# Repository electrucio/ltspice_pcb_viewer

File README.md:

# ltspice_pcb_viewer

Umbrella project for visualizing and cross-exploring electronics designs
(LTspice / KiCad schematics and PCBs). The project is composed of independent
**modules** under [`modules/`](modules/) that will be integrated into a single
application later.

## Modules

| Module | Description |
| --- | --- |
| [`kicad_schematic_viewer`](modules/kicad_schematic_viewer/) | Framework-agnostic `<kicad-schematic>` web component that parses `.kicad_sch`, computes the netlist in-browser, and renders an interactive SVG with net/component highlighting. |
| [`ltspice_schematic_viewer`](modules/ltspice_schematic_viewer/) | Framework-agnostic `<ltspice-schematic>` web component that parses `.asc` (with an embedded `.asy` symbol library), computes the netlist in-browser, and renders an interactive SVG with net/component highlighting. |
| [`ltspice_kicad_mapper`](modules/ltspice_kicad_mapper/) | `<ltspice-kicad-mapper>` web component that embeds both viewers side by side and builds a 1:1 net/component mapping between an LTspice and a KiCad schematic, with JSON import/export. The first cross-module integration. |
| [`kicad_pcb_viewer`](modules/kicad_pcb_viewer/) | `<kicad-pcb>` web component that renders a KiCad `.kicad_pcb` as a single all-layers view (layer toggles, mirror, pan/zoom) with net/component highlighting. |
| [`app`](modules/app/) | The integrated **application**: LTspice on the left, a switchable KiCad schematic/PCB on the right; map nets/components with synchronized cross-probe highlighting; **download a read-only single-file HTML** (iOS-Safari-12-compatible) of the current designs + mapping. |

_The `app` module is the first full integration; more building-block modules may still follow._

The two schematic viewers share the same interaction model and `ksv-*` theming
conventions; their net engines are cross-validated against each other on the shared
guitar-amplifier power-amp design.

## Working on a module

Each module is self-contained (its own `package.json`, build, tests, and demo):

```bash
cd modules/kicad_schematic_viewer
npm install
npm run dev     # interactive demo
npm test        # unit tests
npm run build   # library bundle in dist/
```

## Layout

```
ltspice_pcb_viewer/
  modules/
    kicad_schematic_viewer/     # KiCad schematic net/component viewer
    ltspice_schematic_viewer/   # LTspice schematic net/component viewer
    ltspice_kicad_mapper/       # side-by-side net/component mapper (embeds both viewers)
    kicad_pcb_viewer/           # KiCad .kicad_pcb viewer (all layers, toggles, highlight)
    app/                        # integrated app: map + cross-probe + read-only HTML export
  README.md
```

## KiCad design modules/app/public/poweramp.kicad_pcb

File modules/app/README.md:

# app — LTspice ↔ KiCad mapper & cross-probe

The integrated application that ties the other modules together:

- **Left:** an LTspice schematic. **Right:** a KiCad project, switchable between its
  **schematic** and its **PCB** (a `[Schematic | PCB]` toggle).
- **Map** nets and components between LTspice and KiCad, with **synchronized
  highlighting**: click a net/component in any pane and its mapped counterpart lights up
  in the others — including the PCB (KiCad schematic and PCB share refs; net names are
  reconciled, e.g. schematic `POW` ↔ PCB `/POW`).
- **Simulation summaries**: upload an LTspice transient `.raw` (+ optional `.op.raw`);
  the app summarizes each net (V min/avg/rms/max/pp, DC bias) and component (current,
  voltage drop, power; transistor Ic/Ib/Ie + β) and **discards the bulk waveform**. Hover
  any net/component (either side) to see its metrics in a tooltip; the `ƒ directives` button
  lists the SPICE directives, and the summary rides along in the exported HTML.
  Optionally **Load .log** — the `.raw` stores float32, so harmonics/THD/ripple can't be
  recomputed to LTspice's precision; instead the `.log`'s **exact** `.four` (harmonics +
  THD, signal *and* 50 Hz ripple) and `.meas` results are parsed and shown verbatim in a
  **"from LTspice .log"** section of the tooltip (`sim/logfile.ts`).
  Optionally **Load .net** (the LTspice SPICE netlist) too: unlabeled nets get
  viewer-invented names (`Net-(C14.1)`) that don't match the `.raw`'s internal node names
  (`V(n008)`), so they'd otherwise show no data; the netlist bridges them by matching each
  net to the node touching the same component set (`sim/netlist.ts`) — this also lets the
  `.log`'s node data attach to anonymous nets.
- **Upload** any `.asc`, `.kicad_sch`, and `.kicad_pcb` (toolbar Load buttons).
- **Download read-only HTML**: bakes the current designs + mapping into **one
  self-contained file** that is **read-only** (cross-probe by clicking the schematics/PCB
  or the **nets/components lists**, plus the schematic/PCB toggle and PCB **Mirror** /
  **Rotate** (90°/180°/270°) controls — no editing) and **compatible with old iOS
  Safari (12.x)**.

The app itself targets modern browsers; only the downloaded file carries the old-Safari
constraint.

## Run

```bash
npm install
npm run dev     # builds the export template, then serves the app (modern browsers)
npm run build   # dist-app/ (modern static build)
```

`npm run dev`/`build` first run `npm run build:viewer`, which compiles the read-only
viewer (`viewer/`) into a single Safari-12-targeted HTML *template*
(`src/generated/viewer.html`, git-ignored). The app imports that template with `?raw`
and, on **Download**, replaces its `__LK_DATA__` placeholder with a JSON payload of the
current designs + mapping (ibom-style data-in-a-`<script>`-block; no `fetch`).

## How the pieces fit

```
index.html + src/main.ts            app shell: toolbar (Download) + <ltspice-kicad-mapper>
  └─ <ltspice-kicad-mapper>          embeds <ltspice-schematic>, <kicad-schematic>,
                                     <kicad-pcb>; owns mapping + synchronized highlight
viewer/  (read-only export)         viewer.html + viewer.ts + cross-probe.ts
                                     + lists.ts (read-only sidebars) + compat.ts
  └─ compiled by vite.viewer.config.ts (target: safari12) → src/generated/viewer.html
```

### Old-Safari compatibility (export only)

- `vite.viewer.config.ts` sets esbuild `build.target: "safari12"` → modern **syntax**
  (`?.`, `??`, …) is downleveled automatically.
- `viewer/compat.ts` shims the two **method**-level gaps the viewer components use that
  esbuild does not polyfill: `Element.prototype.replaceChildren` (Safari 14+) and
  `Array.prototype.flatMap`.
- Rendering is **SVG** (no canvas `Path2D`); Web Components / Shadow DOM are native in
  iOS Safari 10.1+; no web-components polyfill is needed for the iOS 12 target.

## Deploying the app (GitHub Pages)

The app is a pure client-side SPA (no backend; static asset `fetch()` calls are
page-relative), so it can be served as-is from GitHub Pages. It's published to
`electrucio.github.io/ltspice-kicad-mapper/` by `.github/workflows/deploy-app.yml`,
which builds `modules/app` with `VITE_BASE=/ltspice-kicad-mapper/` (see `vite.config.ts`
— the built `index.html` otherwise references assets from the site **root**, which
would collide with the other content already at `electrucio.github.io`'s root) and
pushes `dist-app/` into that subfolder of the `electrucio/electrucio.github.io` repo.

One-time setup (must be done by a human on github.com — not automatable from here):

1. **Push this repo to GitHub** (it currently only exists locally): create a repo (e.g.
   under the `electrucio` account) and `git remote add origin <url> && git push -u origin main`.
2. **Create a deploy token**: a classic PAT with `repo` scope, or a fine-grained PAT
   scoped to `electrucio/electrucio.github.io` with **Contents: read and write** —
   created on the account that has push access to that repo.
3. **Add it as a secret** named `PAGES_DEPLOY_TOKEN` in this repo's
   **Settings → Secrets and variables → Actions**.
4. Push to `main` (touching `modules/app/**` or a sibling viewer module) — the workflow
   builds and deploys automatically. Use the **Run workflow** button (workflow_dispatch)
   for a manual first run.

To change the target subfolder or repo, edit `DEPLOY_SUBPATH` / the `repository:` field
in `.github/workflows/deploy-app.yml`.

## Future

The export payload reserves a `simulation` field (currently `null`) for upcoming
LTspice simulation results linked to specific nets/components.

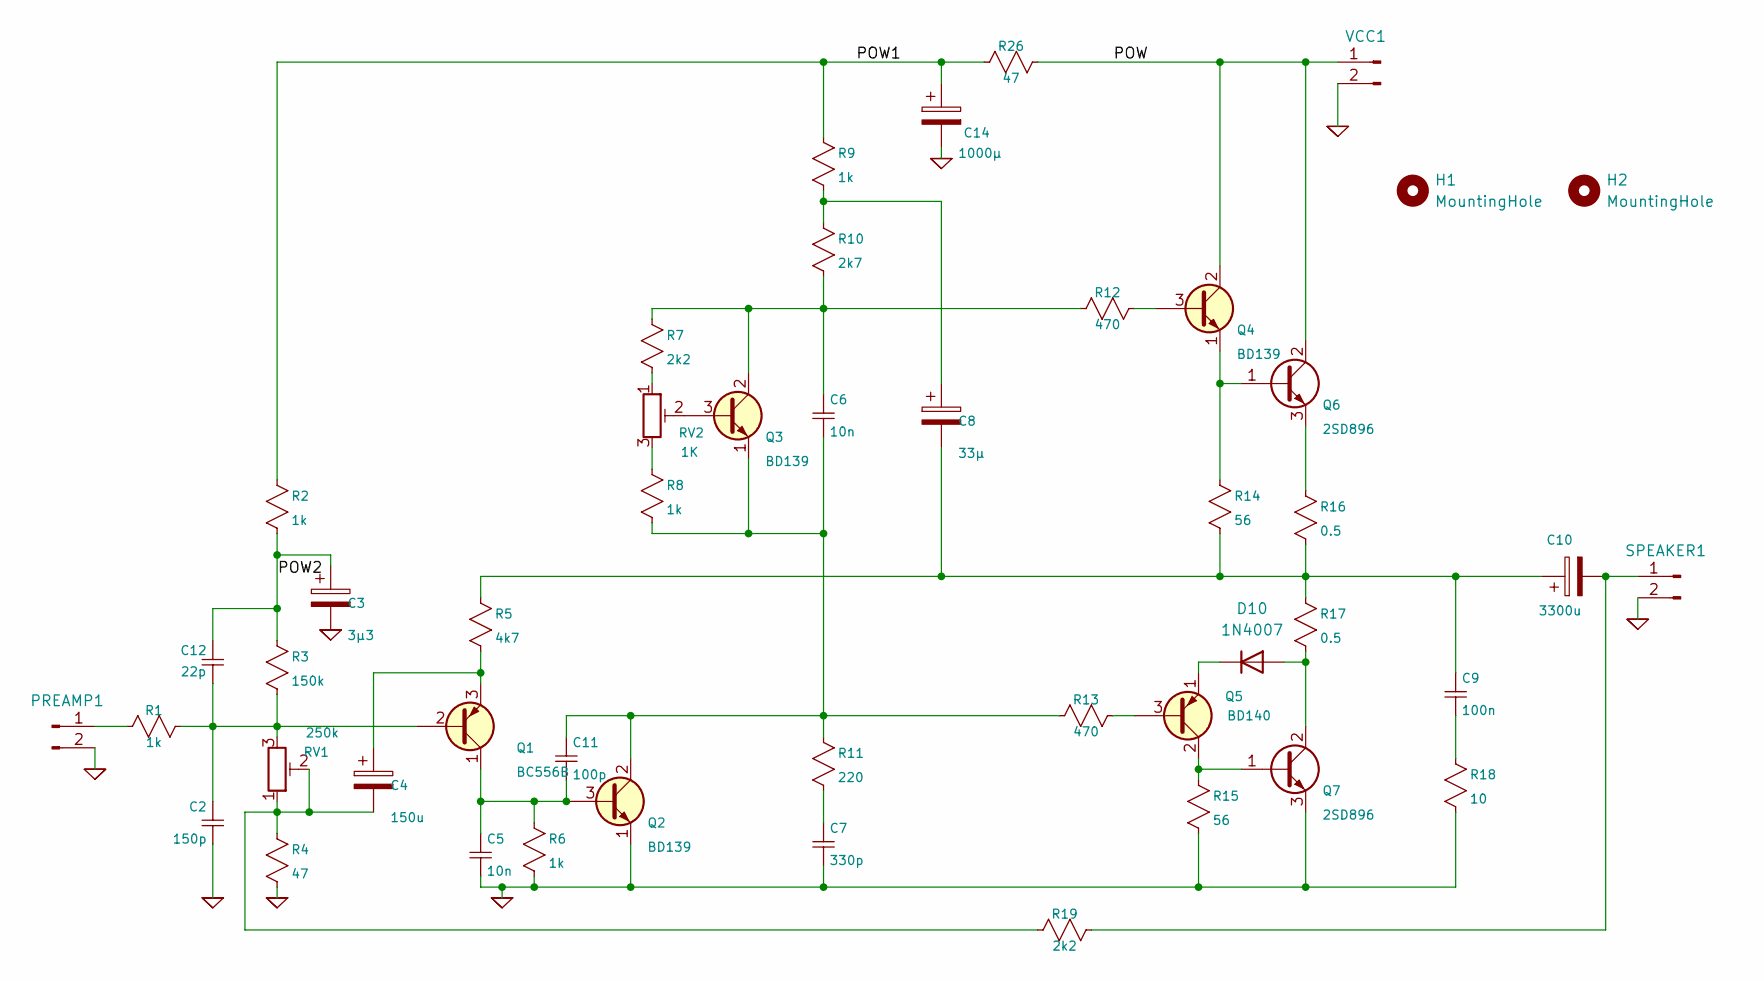
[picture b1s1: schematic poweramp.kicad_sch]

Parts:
C2: 150p; C_Rect_WIMA_1uF_CNC_LargePads
C3: 3µ3; CP_Radial_D6.3mm_P2.50mm
C4: 150u; CP_Radial_220u_8mm_3.5mm_largerpads
C5, C6: 10n; C_Rect_WIMA_1uF_CNC_LargePads
C7: 330p; C_Rect_WIMA_1uF_CNC_LargePads
C8: 33µ; CP_Radial_D8.0mm_P3.80mm
C9: 100n; C_Rect_WIMA_1uF_CNC_LargePads
C10: 3300u; CP_Radial_D22.0mm_P10.00mm_SnapIn
C11: 100p; C_Rect_WIMA_1uF_CNC_LargePads
C12: 22p; C_Disc_D4.3mm_W1.9mm_P5.00mm_largerpads
C14: 1000µ; CP_Radial_220u_12.5mm_5mm_largerpads
D10: 1N4007; D_DO-41_SOD81_P10.16mm_Horizontal
H1, H2: MountingHole; MountingHole_3.5mm
PREAMP1: JST_XH_B2B-XH-A_1x02_P2.50mm_Vertical_ovalpads
Q1: BC556B; TO-92_Inline_Wide_CBE
Q2, Q3, Q4: BD139; TO-126-3_Vertical_ECB
Q5: BD140; TO-126-3_Vertical_ECB
Q6, Q7: 2SD896; TO-3P-3_Vertical_BCE
R1, R2, R6, R8, R9: 1k; R_Axial_DIN0207_L6.3mm_D2.5mm_P10.16mm_Horizontal_LargerPads
R3: 150k; R_Axial_DIN0207_L6.3mm_D2.5mm_P10.16mm_Horizontal_LargerPads
R4: 47; R_Axial_DIN0207_L6.3mm_D2.5mm_P10.16mm_Horizontal_LargerPads
R5: 4k7; R_Axial_DIN0207_L6.3mm_D2.5mm_P10.16mm_Horizontal_LargerPads
R7, R19: 2k2; R_Axial_DIN0207_L6.3mm_D2.5mm_P10.16mm_Horizontal_LargerPads
R10: 2k7; R_Axial_DIN0207_L6.3mm_D2.5mm_P10.16mm_Horizontal_LargerPads
R11: 220; R_Axial_DIN0207_L6.3mm_D2.5mm_P10.16mm_Horizontal_LargerPads
R12, R13: 470; R_Axial_DIN0207_L6.3mm_D2.5mm_P10.16mm_Horizontal_LargerPads
R14, R15: 56; R_Axial_DIN0207_L6.3mm_D2.5mm_P10.16mm_Horizontal_LargerPads
R16, R17: 0.5; R_Axial_Power_L25.0mm_W9.0mm_P30.48mm
R18: 10; R_Axial_DIN0207_L15mm_D5mm_P22mm_Horizontal_LargerPads
R26: 47; R_Axial_DIN0207_L15mm_D5mm_P22mm_Horizontal_LargerPads
RV1: 250k; Potentiometer_Piher_PT-6-V_Vertical_largerpads
RV2: 1K; Potentiometer_Piher_PT-10-V_Vertical_largerpads
SPEAKER1: JST_XH_B2B-XH-A_1x02_P2.50mm_Vertical_ovalpads
VCC1: JST_XH_B2B-XH-A_1x02_P2.50mm_Vertical_ovalpads

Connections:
0: C2.2, C3.2, C5.2, C7.2, C14.2, PREAMP1.2, Q2.1 (E), Q7.3 (E), R4.2, R6.2, R15.2, R18.2, SPEAKER1.2, VCC1.2
/POW: Q4.2 (C), Q6.2 (C), R26.1, VCC1.1
/POW1: C14.1, R2.1, R9.1, R26.2
/POW2: C3.1, C12.1, R2.2, R3.1
unnamed: C4.2, R4.1, R19.2, RV1.1, RV1.2
unnamed: C7.1, R11.2
unnamed: C8.1, R9.2, R10.1
unnamed: C9.2, R18.1
unnamed: C8.2, C9.1, C10.1, R5.1, R14.2, R16.2, R17.1
unnamed: D10.2 (A), Q7.2 (C), R17.2
unnamed: D10.1 (K), Q5.1 (E)
unnamed: PREAMP1.1, R1.2
unnamed: C2.1, C12.2, Q1.2 (B), R1.1, R3.2, RV1.3
unnamed: C5.1, C11.2, Q1.1 (C), Q2.3 (B), R6.1
unnamed: C4.1, Q1.3 (E), R5.2
unnamed 15: C6.2, C11.1, Q2.2 (C), Q3.1 (E), R8.2, R11.1, R13.2; also elsewhere on the board
unnamed 16: Q3.3 (B), RV2.2; also elsewhere on the board
unnamed 17: C6.1, Q3.2 (C), R7.1, R10.2, R12.2; also elsewhere on the board
unnamed: Q4.3 (B), R12.1
unnamed: Q4.1 (E), Q6.1 (B), R14.1
unnamed: Q5.3 (B), R13.1
unnamed: Q5.2 (C), Q7.1 (B), R15.1
unnamed: Q6.3 (E), R16.1
unnamed: R7.2, RV2.1
unnamed: R8.1, RV2.3
unnamed: C10.2, R19.1, SPEAKER1.1

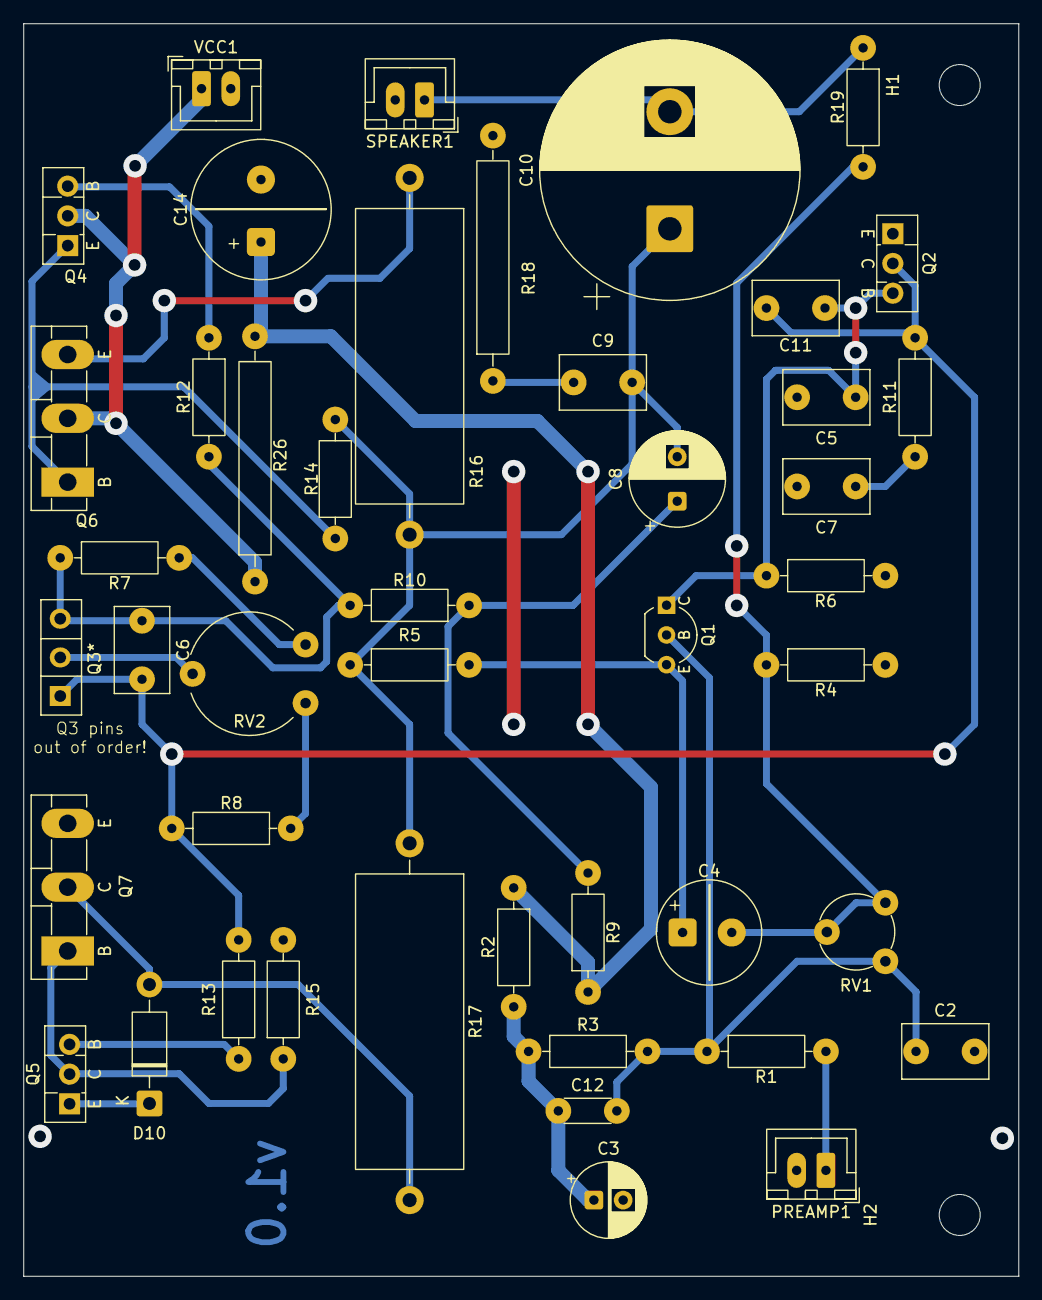
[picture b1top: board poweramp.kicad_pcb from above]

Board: 2 copper layers, 85.0 x 107.0 mm, 47 parts (0 on the bottom side), 26 nets.

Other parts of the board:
Q3*: BD139; TO-126-3_Vertical

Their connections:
unnamed 15: Q3*.1 (E); also elsewhere on the board
unnamed 16: Q3*.3 (B); also elsewhere on the board
unnamed 17: Q3*.2 (C); also elsewhere on the board

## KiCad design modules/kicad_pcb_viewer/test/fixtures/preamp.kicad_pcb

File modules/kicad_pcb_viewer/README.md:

# kicad_pcb_viewer

A framework-agnostic **web component** that renders a KiCad PCB (`.kicad_pcb`) as a
**single combined view of all layers** (not split top/bottom like InteractiveHtmlBom),
with layer toggles, net/component highlighting, mirror, and pan/zoom. Part of the
`ltspice_pcb_viewer` umbrella project; designed for later cross-probe integration.

```html
<kicad-pcb src="board.kicad_pcb"></kicad-pcb>
<script type="module">
  import "kicad_pcb_viewer"; // auto-registers <kicad-pcb>
</script>
```

## What it does

- Parses `.kicad_pcb` (S-expression, reusing the schematic viewer's `sexpr` parser) into
  a render-ready model: board edges, copper tracks, vias, zone fills, and footprints with
  pads + silkscreen + reference labels. Nets are referenced by name (KiCad 9/10).
- Renders one SVG in board mm (Y down): bottom copper, top copper, pads (with drill
  holes), vias, silkscreen, board outline, references — each in a `data-layer` group.
- Every clickable element carries `data-net` / `data-ref`; highlight reuses the
  `--ksv-highlight` variable so the umbrella app can cross-probe like the schematic viewers.

## API

- Attributes: `src`.
- Methods: `loadFromUrl`, `loadFromString`, `getLayers()`, `setLayer(layer, visible)`,
  `setMirror(on)`, `toggleMirror()`, `setRotation(deg)`, `getRotation()`, `rotate90()`,
  `fit()`, `highlightNet(name)`, `highlightComponent(ref)`, `clearHighlights()`,
  `getNets()`, `getComponents()`.
- Events: `ready`, `netselect`, `componentselect`, `nethover`.

Layer ids (toggleable): `B.Cu`, `F.Cu`, `pads`, `vias`, `B.SilkS`, `F.SilkS`,
`Edge.Cuts`, `refs`.

## Develop

```bash
npm install
npm run dev     # demo: poweramp.kicad_pcb (layer checkboxes, net/part lists, mirror)
npm test        # parser tests (counts + pad-on-track coincidence)
npm run build   # library bundle in dist/
```

## Export the demo as a static page

`npm run build:demo` bundles the demo into a **single self-contained**
`dist-demo/index.html` (JS, CSS, and the default `poweramp.kicad_pcb` all inlined —
no runtime `fetch`). It uses a relative `base`, so it works at any URL or subpath:

```bash
# bake YOUR board into the page (defaults to the bundled poweramp board):
BOARD=/path/to/your.kicad_pcb npm run build:demo

# then publish the one file anywhere static, e.g. a GitHub Pages repo:
cp dist-demo/index.html /path/to/<user>.github.io/pcb.html
# it even opens straight from file://
```

The in-page file picker still works on the static page (it reads the chosen
`.kicad_pcb` locally in the browser — nothing is uploaded), so one published
page can also view other boards on the fly.

## Notes / limitations (v1)
- The footprint/pad rotation sign (`ROT_SIGN`) is locked empirically (pads coincide with
  their nets' track endpoints). All poweramp footprints are front-side & through-hole;
  back-side footprint flipping isn't exercised yet (the parser places by orientation only).
- Pad shapes: circle / oval / roundrect / rect (trapezoid/custom fall back to rect).
- Mirror is a horizontal flip of the whole view (text included), i.e. "view from back".
- No copper-pour hatching, soldermask, or 3D; zones render as their filled polygons.

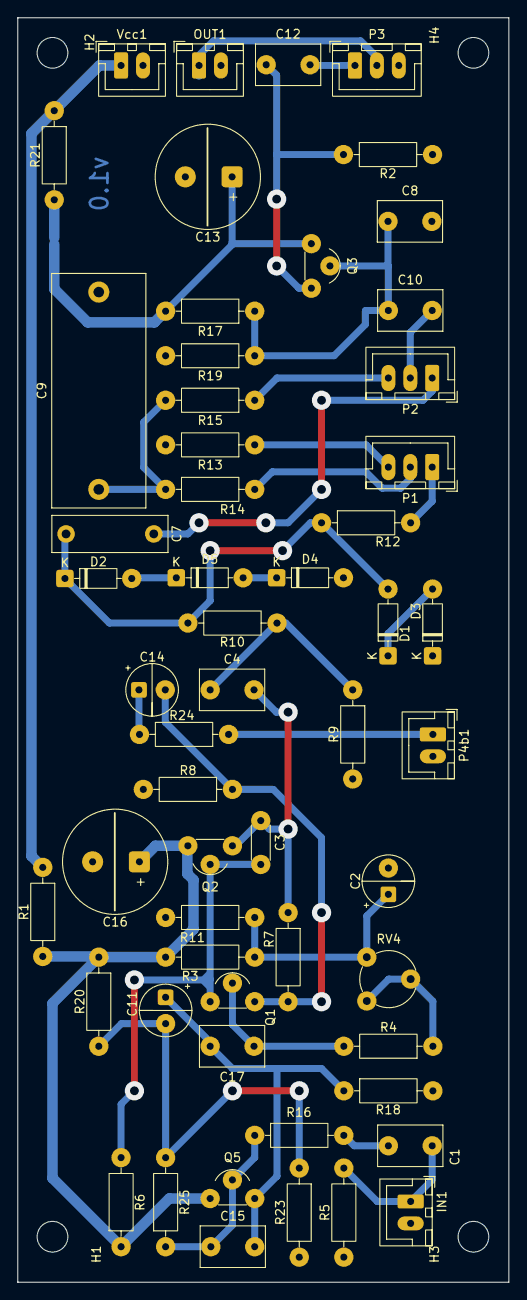
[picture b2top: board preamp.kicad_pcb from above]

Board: 2 copper layers, 56.0 x 144.2 mm, 60 parts (0 on the bottom side), 33 nets.

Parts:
C1, C4, C10, C12, C17: 1µ; C_Rect_WIMA_1uF_CNC_LargePads
C2, C14: 47µ; CP_Radial_D5.0mm_P2.00mm_largerpads
C3: 47p; C_Disc_D4.3mm_W1.9mm_P5.00mm_largerpads
C7: 15n; C_Rect_L13.0mm_W4.0mm_P10.00mm_FKS3_FKP3_MKS4
C8: 100p; C_Rect_WIMA_1uF_CNC_LargePads
C9: 470n; C_Rect_L26.5mm_W10.5mm_P22.50mm_MKS4
C11: 4µ7; CP_Radial_D5.0mm_P2.00mm_largerpads
C13, C16: 470µ; CP_Radial_220u_12.5mm_5mm_largerpads
C15: 1n; C_Rect_WIMA_1uF_CNC_LargePads
D1, D2, D3, D4, D5: 1N4148; D_DO-35_SOD27_P7.62mm_Horizontal_largerpads
H1, H2, H3, H4: MountingHole; MountingHole_3.5mm
IN1: JST_XH_B2B-XH-A_1x02_P2.50mm_Vertical_ovalpads
OUT1: JST_XH_B2B-XH-A_1x02_P2.50mm_Vertical_ovalpads
P1, P2, P3: JST_XH_B3B-XH-A_1x03_P2.50mm_Vertical_ovalpads
P4b1: JST_XH_B2B-XH-A_1x02_P2.50mm_Vertical_ovalpads
Q1, Q3, Q5: BC546B; TO-92_Inline_Wide_largerpads
Q2: BC556B; TO-92_Inline_Wide_largerpads
R1, R13, R21: 100; R_Axial_DIN0207_L6.3mm_D2.5mm_P10.16mm_Horizontal_LargerPads
R2, R12, R18: 10k; R_Axial_DIN0207_L6.3mm_D2.5mm_P10.16mm_Horizontal_LargerPads
R3: 56k; R_Axial_DIN0207_L6.3mm_D2.5mm_P10.16mm_Horizontal_LargerPads
R4: 200K; R_Axial_DIN0207_L6.3mm_D2.5mm_P10.16mm_Horizontal_LargerPads
R5: 10Meg; R_Axial_DIN0207_L6.3mm_D2.5mm_P10.16mm_Horizontal_LargerPads
R6: 2K2; R_Axial_DIN0207_L6.3mm_D2.5mm_P10.16mm_Horizontal_LargerPads
R7: 620; R_Axial_DIN0207_L6.3mm_D2.5mm_P10.16mm_Horizontal_LargerPads
R8: 330; R_Axial_DIN0207_L6.3mm_D2.5mm_P10.16mm_Horizontal_LargerPads
R9: 47k; R_Axial_DIN0207_L6.3mm_D2.5mm_P10.16mm_Horizontal_LargerPads
R10: 470; R_Axial_DIN0207_L6.3mm_D2.5mm_P10.16mm_Horizontal_LargerPads
R11: 22k; R_Axial_DIN0207_L6.3mm_D2.5mm_P10.16mm_Horizontal_LargerPads
R14, R15: 47; R_Axial_DIN0207_L6.3mm_D2.5mm_P10.16mm_Horizontal_LargerPads
R16: 1k; R_Axial_DIN0207_L6.3mm_D2.5mm_P10.16mm_Horizontal_LargerPads
R17: 330K; R_Axial_DIN0207_L6.3mm_D2.5mm_P10.16mm_Horizontal_LargerPads
R19: 110k; R_Axial_DIN0207_L6.3mm_D2.5mm_P10.16mm_Horizontal_LargerPads
R20, R25: 120k; R_Axial_DIN0207_L6.3mm_D2.5mm_P10.16mm_Horizontal_LargerPads
R23: 200k; R_Axial_DIN0207_L6.3mm_D2.5mm_P10.16mm_Horizontal_LargerPads
R24: 22; R_Axial_DIN0207_L6.3mm_D2.5mm_P10.16mm_Horizontal_LargerPads
RV4: 47k; Potentiometer_Piher_PT-6-V_Vertical_largerpads
Vcc1: JST_XH_B2B-XH-A_1x02_P2.50mm_Vertical_ovalpads

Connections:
0: C2.2, C8.2, C9.2, C13.2, C16.2, D3.1 (+), D4.2 (-), IN1.2, OUT1.2, P3.3, P4b1.2, R2.2, R5.2, R8.2, R9.2, R11.2, R13.2, R18.2, R19.2, R23.2, Vcc1.2
/POW: R1.1, R21.1, Vcc1.1
/POW_Q2Q5: C16.1, Q2.3 (E), Q5.1 (C), R1.2, R3.1, R6.1, R20.1
/POW_Q3: C13.1, Q3.1 (C), R17.2, R21.2
unnamed: C1.1, R16.2
unnamed: C2.1, R3.2, R11.1, RV4.3
unnamed: C4.1, R9.1, R10.2
unnamed: C9.1, R14.1, R15.2
unnamed: C11.2, R20.2, R23.1, R25.2
unnamed: C14.1, R24.2
unnamed: D1.1 (+), D3.2 (-)
unnamed: C7.2, D1.2 (-), D2.1 (+), R10.1, R12.1
unnamed: D2.2 (-), D5.1 (+)
unnamed: D4.1 (+), D5.2 (-)
unnamed: C1.2, IN1.1, R5.1
unnamed: OUT1.1, P3.2
unnamed: P1.1, R12.2
unnamed: P1.2, R14.2
unnamed: P1.3, R13.1
unnamed: C7.1, P2.1
unnamed: C10.2, P2.2
unnamed: P2.3, R15.1
unnamed: C12.2, P3.1
unnamed: P4b1.1, R24.1
unnamed: C17.1, Q1.2 (B), R4.2
unnamed: C3.2, Q1.1 (C), Q2.2 (B), R6.2
unnamed: C14.2, Q1.3 (E), R7.2, R8.1
unnamed: C3.1, C4.2, Q2.1 (C), R7.1
unnamed: C8.1, C10.1, Q3.2 (B), R17.1, R19.1
unnamed: C12.1, Q3.3 (E), R2.1
unnamed: C15.1, Q5.2 (B), R16.1, R25.1
unnamed: C11.1, C15.2, C17.2, Q5.3 (E), R18.1
unnamed: R4.1, RV4.1, RV4.2

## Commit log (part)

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2026-06-28 Revert "Mapper: net similarity uses only confirmed components (fix VCC->Net-(Q4-E))"
    This reverts commit dd9a238cba2f61e3fcc645a2a35e8336963be5f4.
